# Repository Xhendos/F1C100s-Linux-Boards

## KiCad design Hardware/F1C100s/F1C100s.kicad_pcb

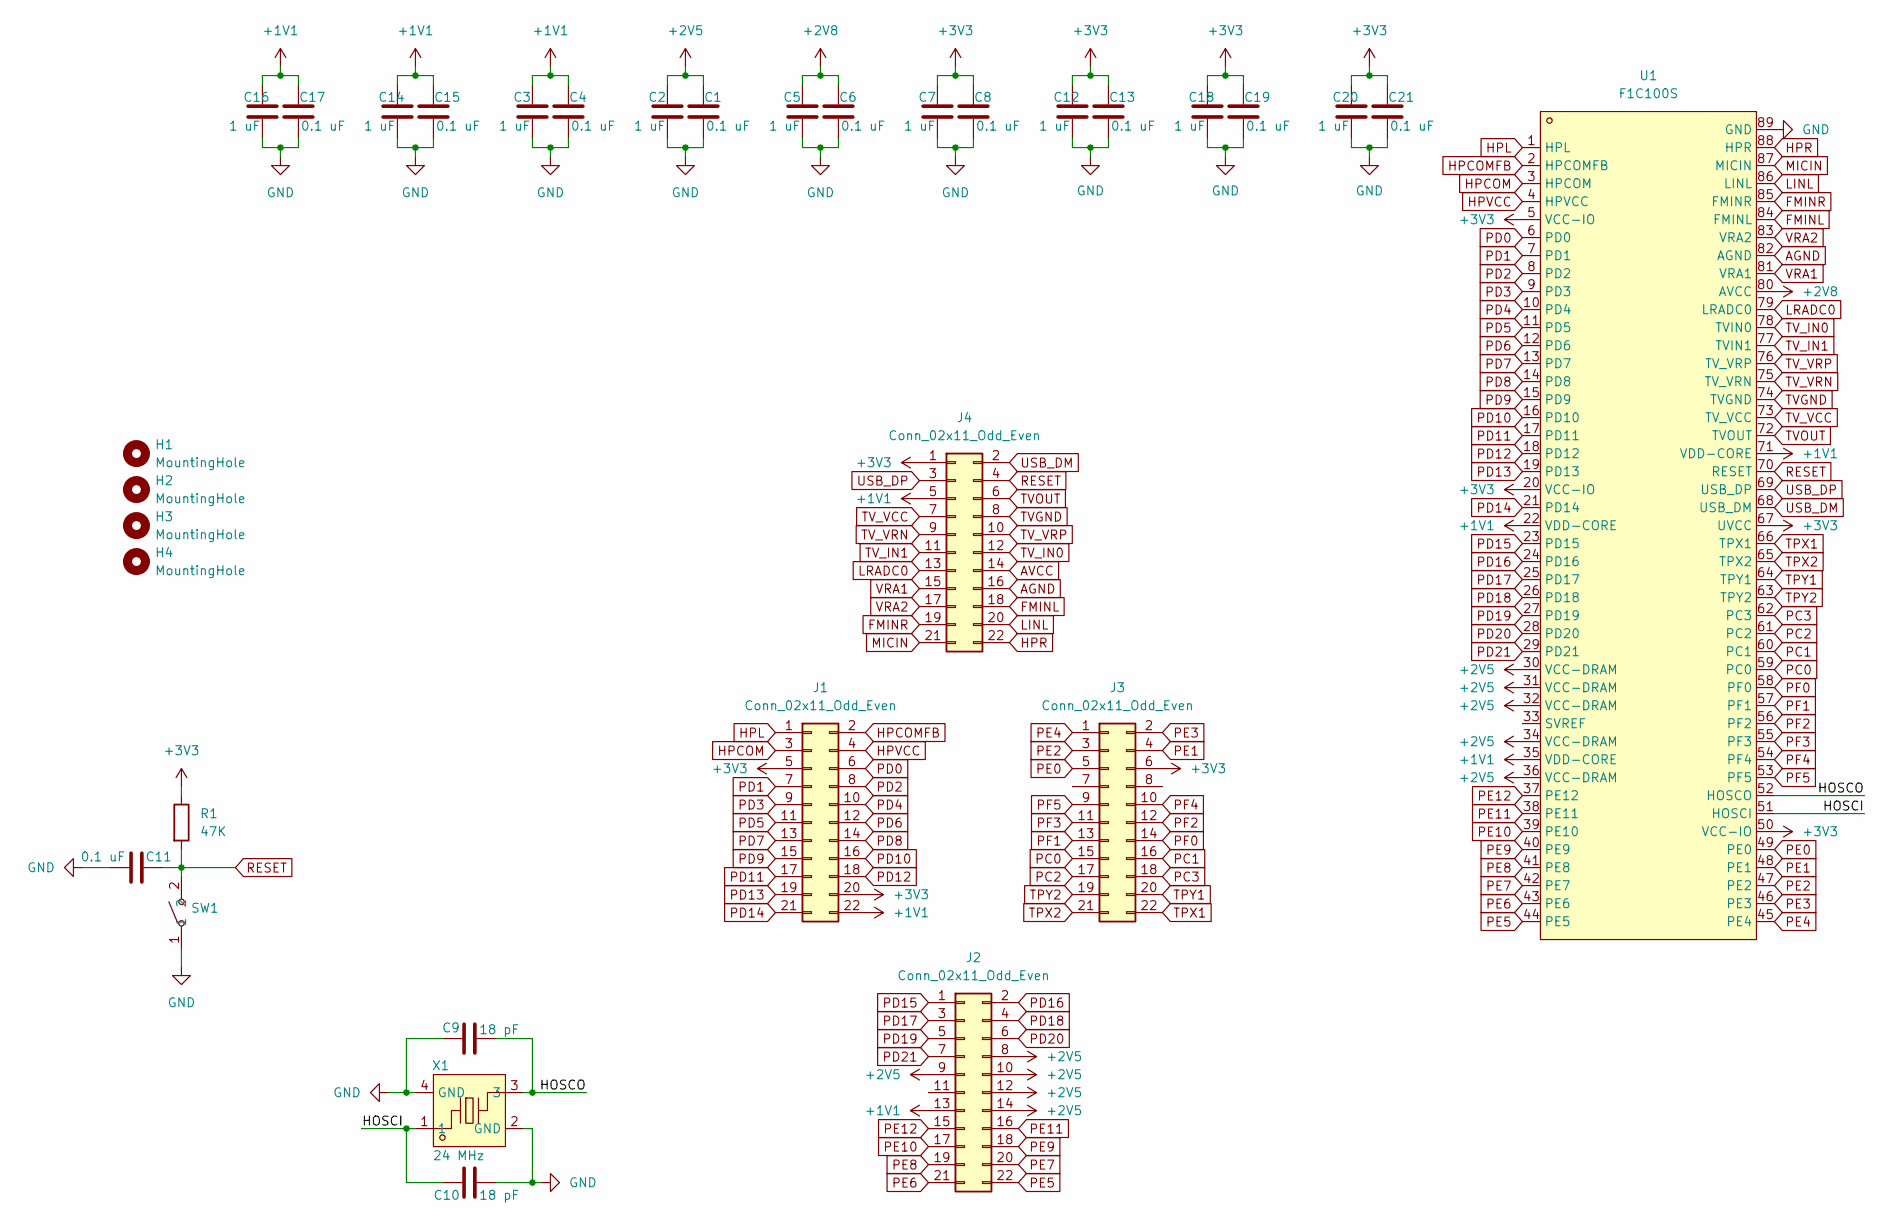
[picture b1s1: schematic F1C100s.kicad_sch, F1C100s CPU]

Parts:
C1, C4, C6, C8, C11, C13, C15, C17, C19, C21: 0.1 uF; C_0201_0603Metric_Pad0.64x0.40mm_HandSolder
C2, C3, C5, C7, C12, C14, C16, C18, C20: 1 uF; C_0201_0603Metric_Pad0.64x0.40mm_HandSolder
C9, C10: 18 pF; C_0201_0603Metric_Pad0.64x0.40mm_HandSolder
H1, H2, H3, H4: MountingHole; MountingHole_2.7mm_M2.5
J1, J2, J3, J4: Conn_02x11_Odd_Even; PinSocket_2x11_P2.54mm_Vertical
R1: 47K; R_0201_0603Metric_Pad0.64x0.40mm_HandSolder
SW1: SW-SMD_L3.9-W3.0-P4.45; LCSC Part C455280
U1: F1C100S; QFN-88_L10.0-W10.0-P0.40-BL-EP6.75; LCSC Part C1511928
X1: 24 MHz; CRYSTAL-SMD_4P-L3.2-W2.5-BL; LCSC Part C20617586

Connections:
+1V1: C3.1, C4.1, C14.1, C15.1, C16.1, C17.1, J1.22, J2.13, J4.5, U1.22 (VDD-CORE), U1.35 (VDD-CORE), U1.71 (VDD-CORE)
+2V5: C1.1, C2.1, J2.8, J2.9, J2.10, J2.12, J2.14, U1.30 (VCC-DRAM), U1.31 (VCC-DRAM), U1.32 (VCC-DRAM), U1.34 (VCC-DRAM), U1.36 (VCC-DRAM)
+2V8: C5.1, C6.1, U1.80 (AVCC)
+3V3: C7.1, C8.1, C12.1, C13.1, C18.1, C19.1, C20.1, C21.1, J1.5, J1.20, J3.6, J4.1, R1.1, U1.5 (VCC-IO), U1.20 (VCC-IO), U1.50 (VCC-IO), U1.67 (UVCC)
/HOSCI: C10.1, U1.51 (HOSCI), X1.1
/HOSCO: C9.2, U1.52 (HOSCO), X1.3
AGND: J4.16, U1.82 (AGND)
AVCC: J4.14
FMINL: J4.18, U1.84 (FMINL)
FMINR: J4.19, U1.85 (FMINR)
GND: C1.2, C2.2, C3.2, C4.2, C5.2, C6.2, C7.2, C8.2, C9.1, C10.2, C11.1, C12.2, C13.2, C14.2, C15.2, C16.2, C17.2, C18.2, C19.2, C20.2, C21.2, SW1.1, U1.89 (GND), X1.2 (GND), X1.4 (GND)
HPCOM: J1.3, U1.3 (HPCOM)
HPCOMFB: J1.2, U1.2 (HPCOMFB)
HPL: J1.1, U1.1 (HPL)
HPR: J4.22, U1.88 (HPR)
HPVCC: J1.4, U1.4 (HPVCC)
LINL: J4.20, U1.86 (LINL)
LRADC0: J4.13, U1.79 (LRADC0)
MICIN: J4.21, U1.87 (MICIN)
PC0: J3.15, U1.59 (PC0)
PC1: J3.16, U1.60 (PC1)
PC2: J3.17, U1.61 (PC2)
PC3: J3.18, U1.62 (PC3)
PD0: J1.6, U1.6 (PD0)
PD1: J1.7, U1.7 (PD1)
PD2: J1.8, U1.8 (PD2)
PD3: J1.9, U1.9 (PD3)
PD4: J1.10, U1.10 (PD4)
PD5: J1.11, U1.11 (PD5)
PD6: J1.12, U1.12 (PD6)
PD7: J1.13, U1.13 (PD7)
PD8: J1.14, U1.14 (PD8)
PD9: J1.15, U1.15 (PD9)
PD10: J1.16, U1.16 (PD10)
PD11: J1.17, U1.17 (PD11)
PD12: J1.18, U1.18 (PD12)
PD13: J1.19, U1.19 (PD13)
PD14: J1.21, U1.21 (PD14)
PD15: J2.1, U1.23 (PD15)
PD16: J2.2, U1.24 (PD16)
PD17: J2.3, U1.25 (PD17)
PD18: J2.4, U1.26 (PD18)
PD19: J2.5, U1.27 (PD19)
PD20: J2.6, U1.28 (PD20)
PD21: J2.7, U1.29 (PD21)
PE0: J3.5, U1.49 (PE0)
PE1: J3.4, U1.48 (PE1)
PE2: J3.3, U1.47 (PE2)
PE3: J3.2, U1.46 (PE3)
PE4: J3.1, U1.45 (PE4)
PE5: J2.22, U1.44 (PE5)
PE6: J2.21, U1.43 (PE6)
PE7: J2.20, U1.42 (PE7)
PE8: J2.19, U1.41 (PE8)
PE9: J2.18, U1.40 (PE9)
PE10: J2.17, U1.39 (PE10)
PE11: J2.16, U1.38 (PE11)
PE12: J2.15, U1.37 (PE12)
PF0: J3.14, U1.58 (PF0)
PF1: J3.13, U1.57 (PF1)
PF2: J3.12, U1.56 (PF2)
PF3: J3.11, U1.55 (PF3)
PF4: J3.10, U1.54 (PF4)
PF5: J3.9, U1.53 (PF5)
RESET: C11.2, J4.4, R1.2, SW1.2, U1.70 (RESET)
TPX1: J3.22, U1.66 (TPX1)
TPX2: J3.21, U1.65 (TPX2)
TPY1: J3.20, U1.64 (TPY1)
TPY2: J3.19, U1.63 (TPY2)
TVGND: J4.8, U1.74 (TVGND)
TVOUT: J4.6, U1.72 (TVOUT)
TV_IN0: J4.12, U1.78 (TVIN0)
TV_IN1: J4.11, U1.77 (TVIN1)
TV_VCC: J4.7, U1.73 (TV_VCC)
TV_VRN: J4.9, U1.75 (TV_VRN)
TV_VRP: J4.10, U1.76 (TV_VRP)
USB_DM: J4.2, U1.68 (USB_DM)
USB_DP: J4.3, U1.69 (USB_DP)
VRA1: J4.15, U1.81 (VRA1)
VRA2: J4.17, U1.83 (VRA2)

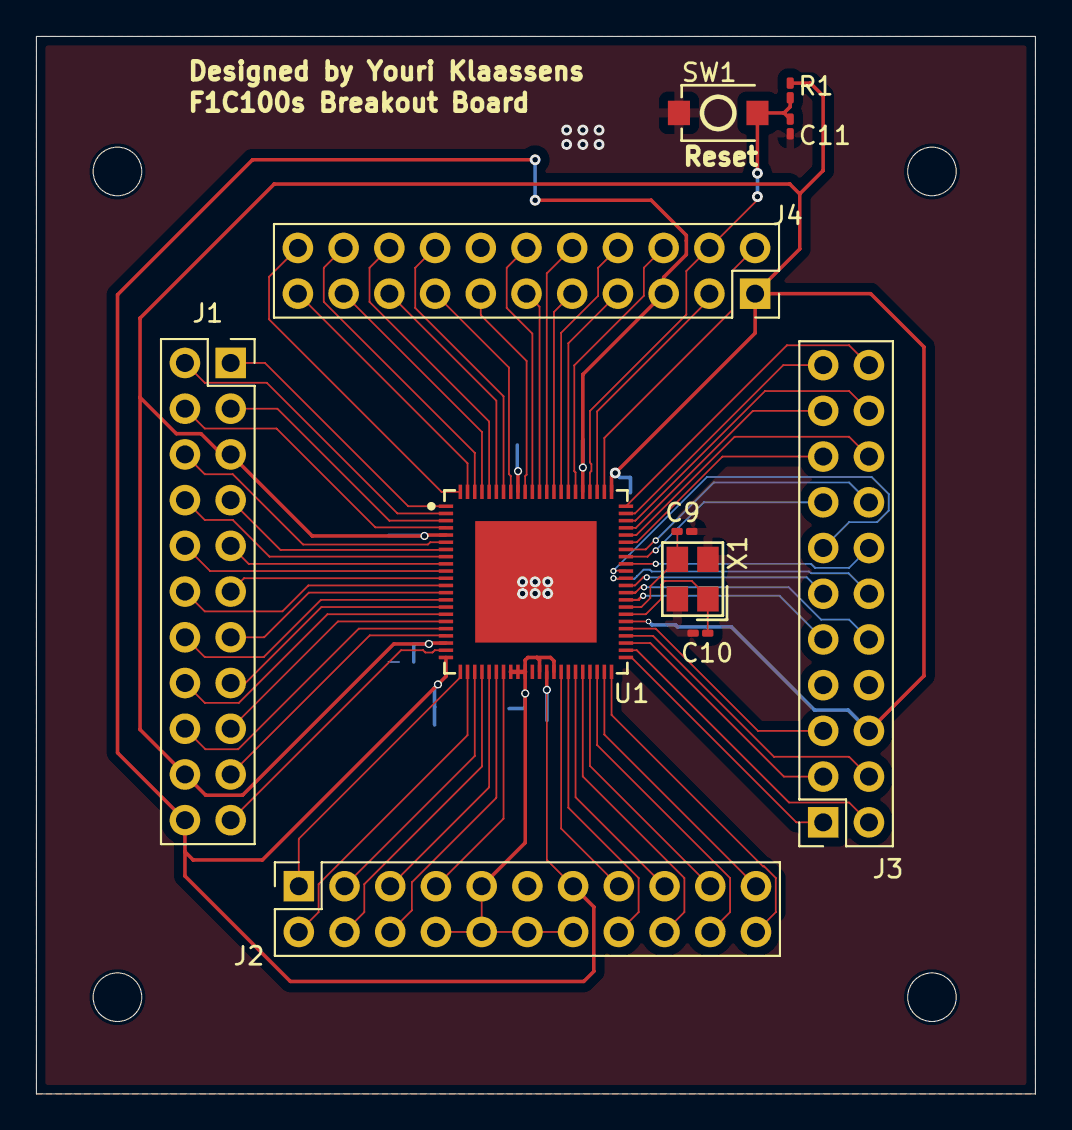
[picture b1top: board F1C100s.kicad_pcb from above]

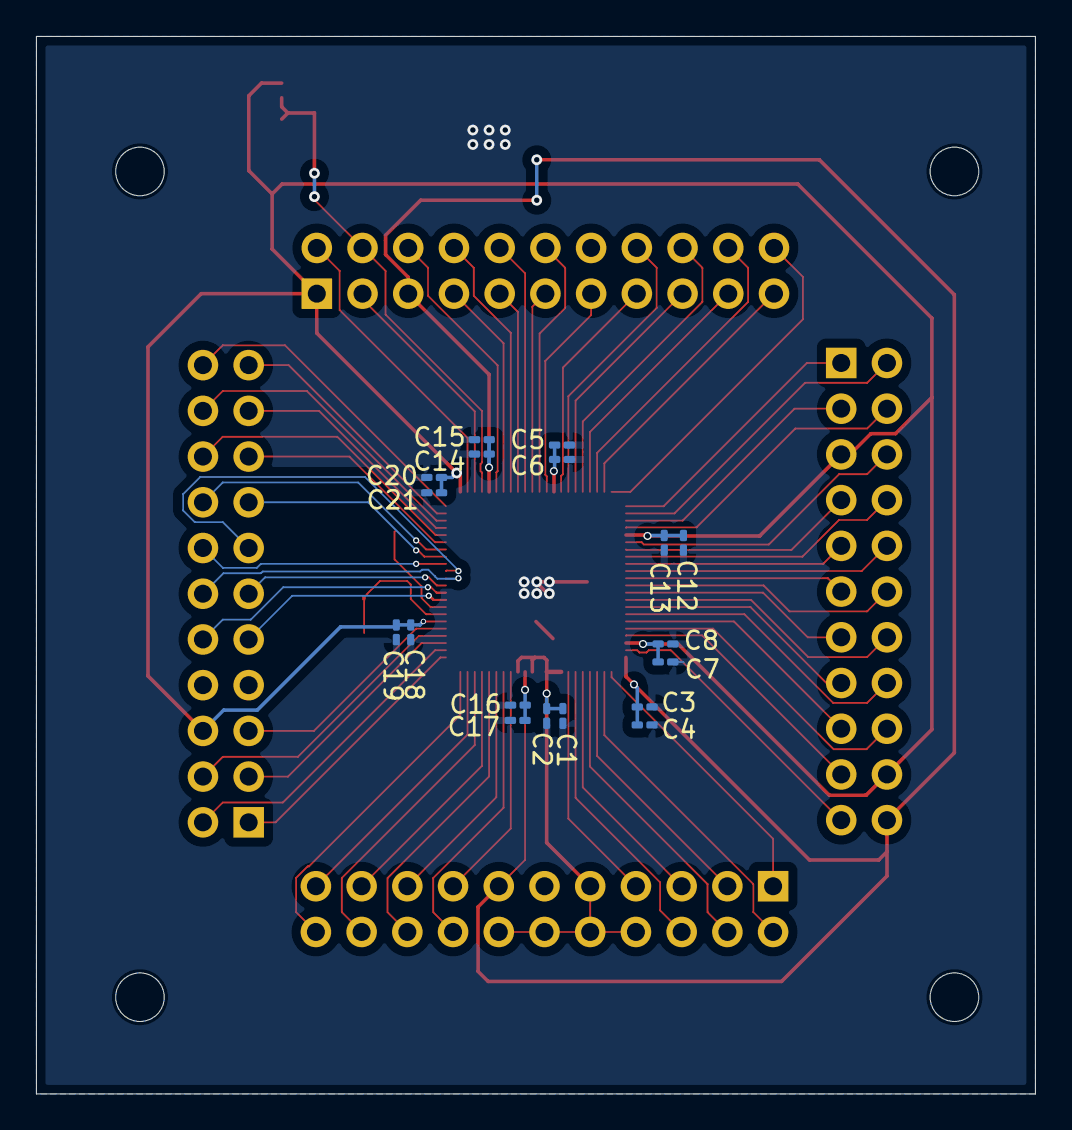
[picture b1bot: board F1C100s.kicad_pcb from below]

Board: 2 copper layers, 55.5 x 58.8 mm, 33 parts (18 on the bottom side), 79 nets.

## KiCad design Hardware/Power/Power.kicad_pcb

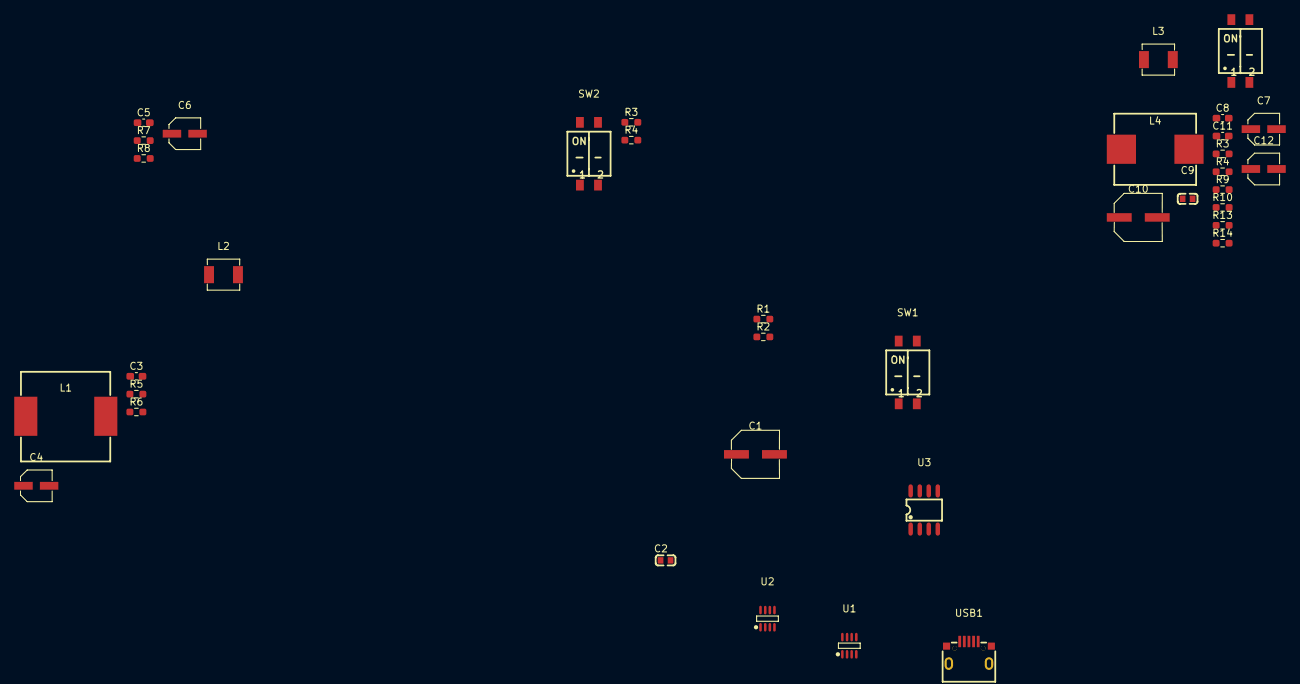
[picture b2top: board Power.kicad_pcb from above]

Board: 2 copper layers, 37 parts (0 on the bottom side), 22 nets, no tracks yet.

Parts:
C1, C10: 100 uF; CAP-SMD_BD6.3-L6.6-W6.6-FD
C2, C9: 10 uF; C0603
C3, C5, C8, C11: 22 pF; C_0603_1608Metric_Pad1.08x0.95mm_HandSolder
C4, C6, C7, C12: 22 uF; CAP-SMD_BD4.0-L4.3-W4.3-LS5.1-FD
L1: 22 uH; IND-SMD_L13.5-W12.6_TMPC1206HP-1R5MG-D
L2, L3: 3.3 uH; IND-SMD_L4.4-W4.2-A
L4: 0.8 uH; IND-SMD_L11.5-W10.0_PSPMAA1040H-330M-ANP
R1, R2, R3, R3#2, R4, R4#2: 1M; R_0603_1608Metric_Pad0.98x0.95mm_HandSolder
R5, R9, R13: 120K; R_0603_1608Metric_Pad0.98x0.95mm_HandSolder
R6, R7: 100K; R_0603_1608Metric_Pad0.98x0.95mm_HandSolder
R8: 316K; R_0603_1608Metric_Pad0.98x0.95mm_HandSolder
R10: 440K; R_0603_1608Metric_Pad0.98x0.95mm_HandSolder
R14: 536K; R_0603_1608Metric_Pad0.98x0.95mm_HandSolder
SW1, SW2, SW2#2: KF1027B-02P-G00-ON-01B; SW-SMD_4P-L6.1-W6.2-P2.54-LS10.0
U1, U2: SY8029AIC; SOT-23-8_L3.0-W1.7-P0.65-LS2.8-BL
U3: CH340N; SOP-8_L4.9-W3.9-P1.27-LS6.0-BL
USB1: USB-MR-D-019; MICRO-USB-SMD_USB-MR-D-017

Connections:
+1V1: C3.2, C4.1, L1.1, R6.2
+2V5: C5.2, C6.1, L2.2, R8.2
+2V8: C7.1, C8.2, L3.1, R10.2
+3V3: C11.2, C12.1, L4.2, R14.2
+5V: SW1.3 (A3), SW1.4 (A4), SW2#2.3 (A3), SW2#2.4 (A4), USB1.1
GND: C1.2, C2.1, C4.2, C6.2, C7.2, C9.1, C10.2, C12.2, R1.2, R2.2, R3.2, R3#2.2, R4.2, R4#2.2, R5.1, R7.1, R9.1, R13.1, USB1.5
unnamed: R1.1, SW1.1 (A1), U2.6 (EN2)
unnamed: R2.1, SW1.2 (A2), U2.7 (EN1)
unnamed: R3.1, SW2#2.1 (A1), U1.6 (EN2)
unnamed: R4#2.1, SW2#2.2 (A2), U1.7 (EN1)
unnamed: C8.1, R9.2, R10.1, U1.1 (FB1)
unnamed: C11.1, R13.2, R14.1, U1.8 (FB2)
unnamed: C9.2, C10.1, U1.2 (IN)
unnamed: L3.2, U1.3 (LX1)
unnamed: L4.1, U1.5 (LX2)
unnamed: C3.1, R5.2, R6.1, U2.1 (FB1)
unnamed: C5.1, R7.2, R8.1, U2.8 (FB2)
unnamed: C1.1, C2.2, U2.2 (IN)
unnamed: L1.2, U2.3 (LX1)
unnamed: L2.1, U2.5 (LX2)
unnamed: U3.1 (UD+), USB1.3
unnamed: U3.2 (UD-), USB1.2

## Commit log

2025-05-14 added most components for Power PCB in the schematic
